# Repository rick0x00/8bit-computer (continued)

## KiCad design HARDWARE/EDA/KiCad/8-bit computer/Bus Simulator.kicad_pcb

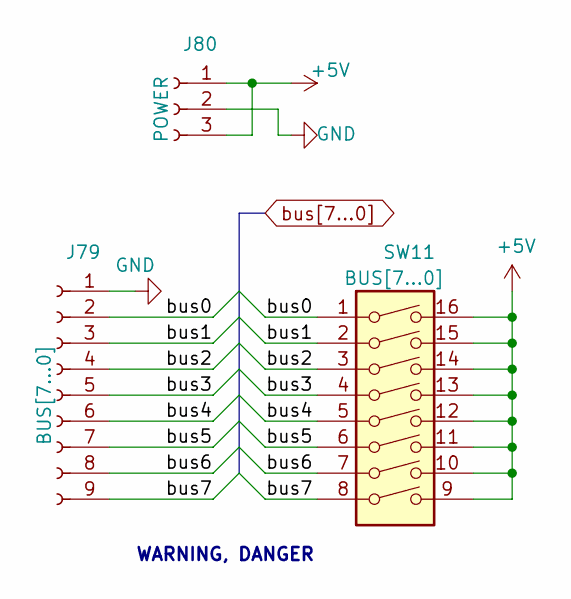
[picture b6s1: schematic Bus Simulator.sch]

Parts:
J79: BUS[7...0]; PinSocket_1x09_P2.00mm_Vertical
J80: POWER; PinSocket_1x03_P2.00mm_Vertical
SW11: BUS[7...0]; SW_DIP_SPSTx08_Slide_9.78x22.5mm_W7.62mm_P2.54mm

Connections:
+5V: J80.1, J80.3, SW11.9, SW11.10, SW11.11, SW11.12, SW11.13, SW11.14, SW11.15, SW11.16
GND: J79.1, J80.2
bus0: J79.2, SW11.1
bus1: J79.3, SW11.2
bus2: J79.4, SW11.3
bus3: J79.5, SW11.4
bus4: J79.6, SW11.5
bus5: J79.7, SW11.6
bus6: J79.8, SW11.7
bus7: J79.9, SW11.8

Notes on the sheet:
WARNING, DANGER

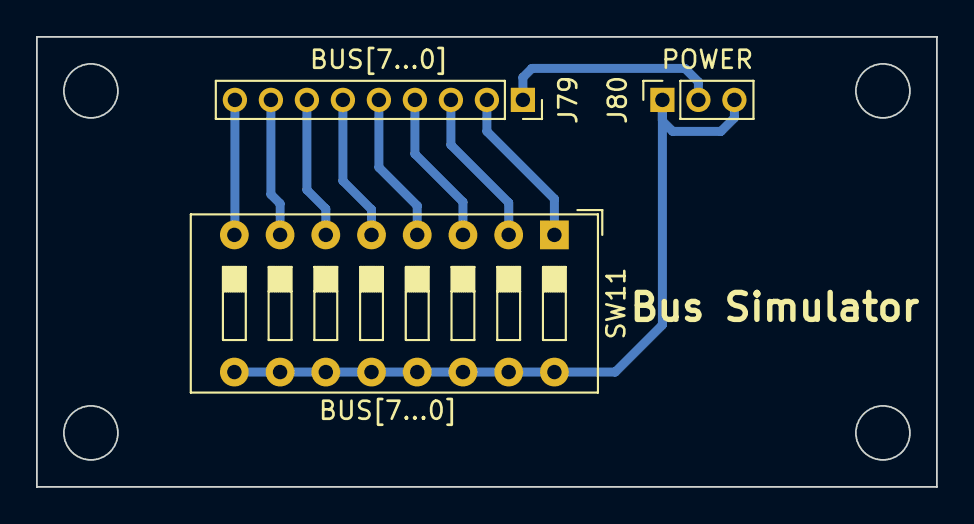
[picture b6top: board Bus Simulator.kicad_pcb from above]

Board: 2 copper layers, 50.0 x 25.0 mm, 3 parts (0 on the bottom side), 10 nets.

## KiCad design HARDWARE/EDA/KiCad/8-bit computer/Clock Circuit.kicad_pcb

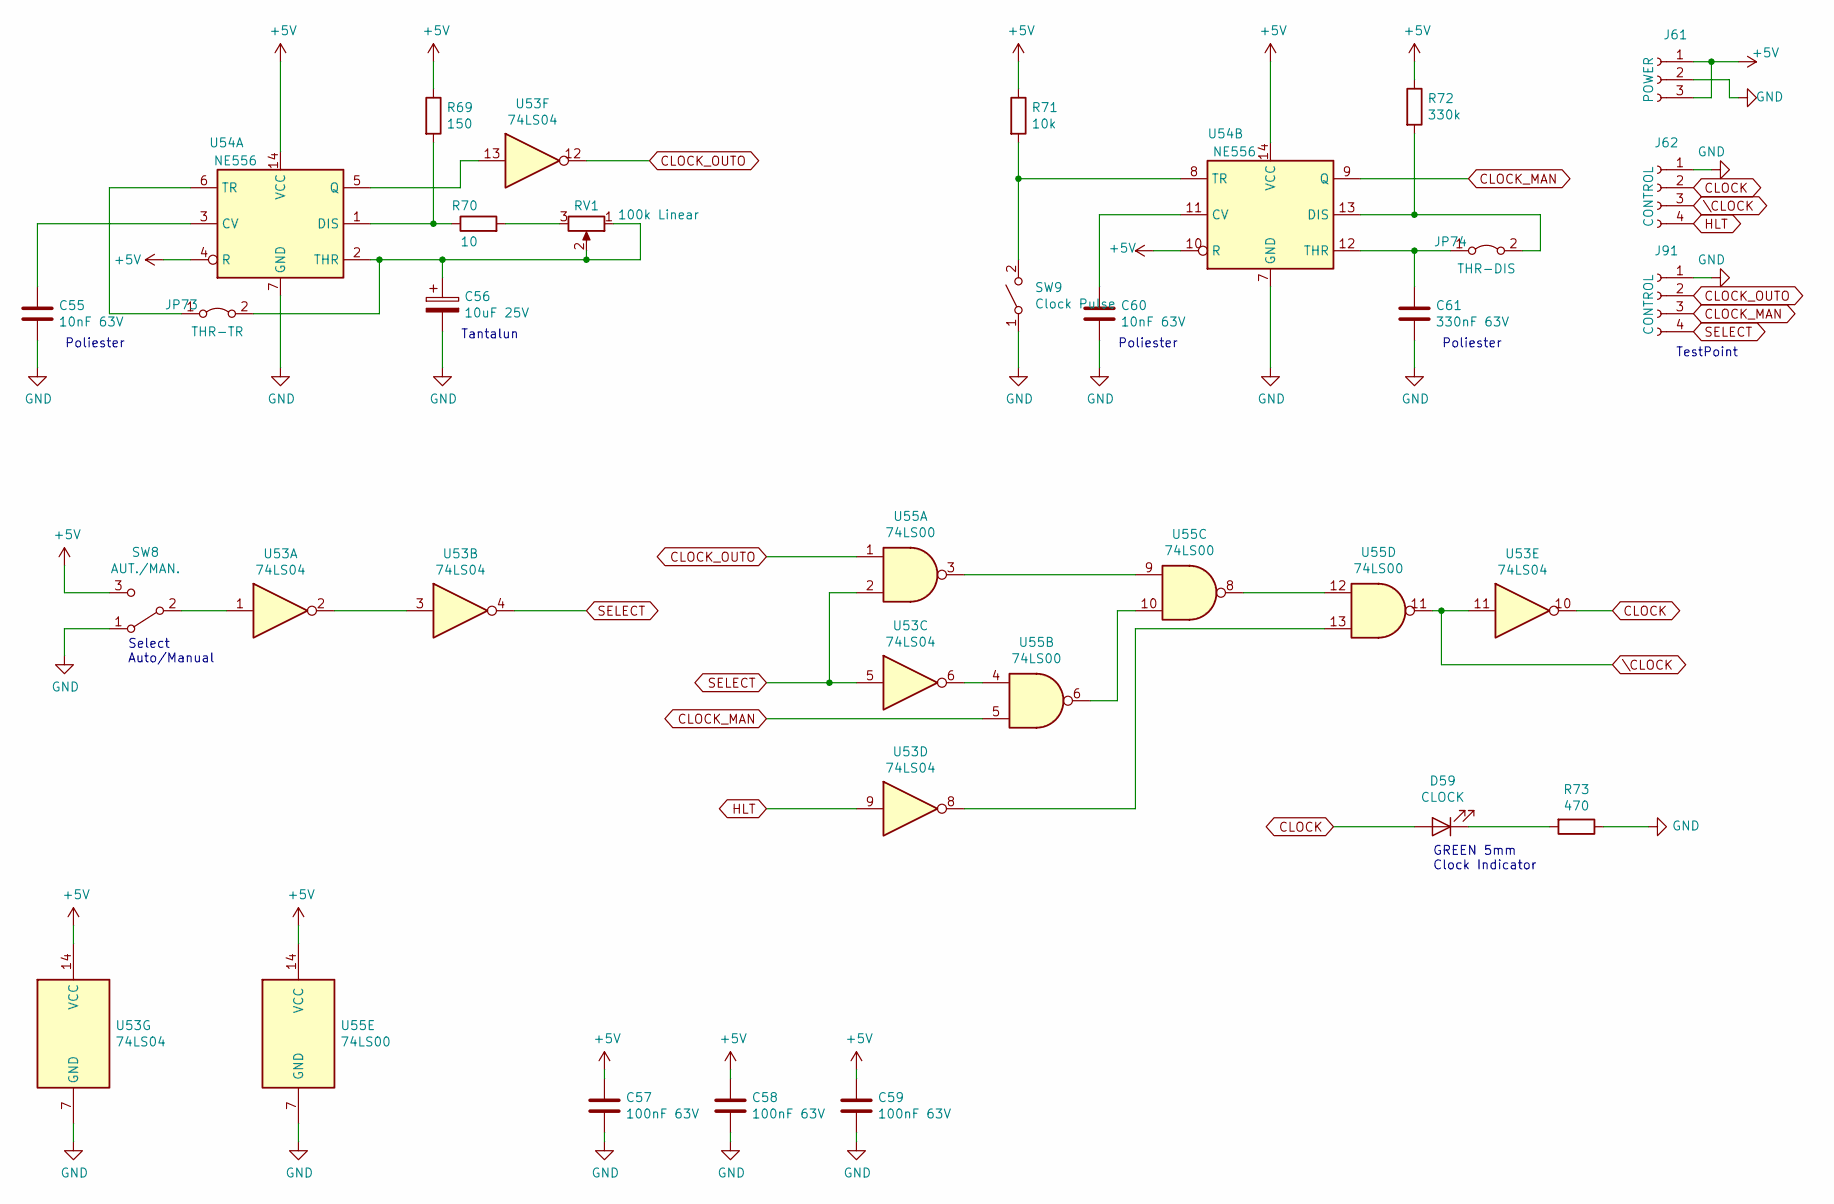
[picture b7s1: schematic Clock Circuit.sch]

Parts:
C55, C60: 10nF 63V; C_Rect_L7.0mm_W2.5mm_P5.00mm
C56: 10uF 25V; CP_Radial_Tantal_D4.5mm_P2.50mm
C57, C58, C59: 100nF 63V; C_Rect_L7.0mm_W2.5mm_P5.00mm
C61: 330nF 63V; C_Rect_L7.0mm_W2.5mm_P5.00mm
D59: CLOCK; LED_D3.0mm
J61: POWER; PinSocket_1x03_P2.00mm_Vertical
J62, J91: CONTROL; PinSocket_1x04_P2.00mm_Vertical
JP73: THR-TR; TestPoint_2Pads_Pitch2.54mm_Drill0.8mm
JP74: THR-DIS; TestPoint_2Pads_Pitch2.54mm_Drill0.8mm
R69: 150; R_Axial_DIN0207_L6.3mm_D2.5mm_P7.62mm_Horizontal
R70: 10; R_Axial_DIN0207_L6.3mm_D2.5mm_P7.62mm_Horizontal
R71: 10k; R_Axial_DIN0207_L6.3mm_D2.5mm_P7.62mm_Horizontal
R72: 330k; R_Axial_DIN0207_L6.3mm_D2.5mm_P7.62mm_Horizontal
R73: 470; R_Axial_DIN0207_L6.3mm_D2.5mm_P7.62mm_Horizontal
RV1: 100k Linear; Potentiometer_Bourns_3266Y_Vertical
SW8: AUT./MAN.; SW_CuK_OS102011MA1QN1_SPDT_Angled
SW9: Clock Pulse; SW_PUSH_6mm_H5mm
U53: 74LS04; DIP-14_W7.62mm_LongPads
U54: NE556; DIP-14_W7.62mm_LongPads
U55: 74LS00; DIP-14_W7.62mm_LongPads

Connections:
+5V: C57.1, C58.1, C59.1, J61.1, J61.3, R69.1, R71.1, R72.1, SW8.3 (C), U53.14 (VCC), U54.4 (R), U54.10 (R), U54.14 (VCC), U55.14 (VCC)
CLOCK: D59.2 (A), J62.2, U53.10
CLOCK_MAN: J91.3, U54.9 (Q), U55.5
CLOCK_OUTO: J91.2, U53.12, U55.1
GND: C55.2, C56.2, C57.2, C58.2, C59.2, C60.2, C61.2, J61.2, J62.1, J91.1, R73.1, SW8.1 (A), SW9.1 (A), U53.7 (GND), U54.7 (GND), U55.7 (GND)
HLT: J62.4, U53.9
unnamed: C55.1, U54.3 (CV)
unnamed: C56.1, JP73.2 (B), RV1.1, RV1.2, U54.2 (THR)
unnamed: C60.1, U54.11 (CV)
unnamed: C61.1, JP74.1 (A), U54.12 (THR)
unnamed: D59.1 (K), R73.2
unnamed: JP73.1 (A), U54.6 (TR)
unnamed: JP74.2 (B), R72.2, U54.13 (DIS)
unnamed: R69.2, R70.1, U54.1 (DIS)
unnamed: R70.2, RV1.3
unnamed: R71.2, SW9.2 (B), U54.8 (TR)
unnamed: SW8.2 (B), U53.1
unnamed: U53.2, U53.3
unnamed: U53.6, U55.4
unnamed: U53.8, U55.13
unnamed: U53.13, U54.5 (Q)
unnamed: U55.3, U55.9
unnamed: U55.6, U55.10
unnamed: U55.8, U55.12
SELECT: J91.4, U53.4, U53.5, U55.2
\CLOCK: J62.3, U53.11, U55.11

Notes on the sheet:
Select Auto/Manual
GREEN 5mm Clock Indicator
Tantalun
Poliester
TestPoint

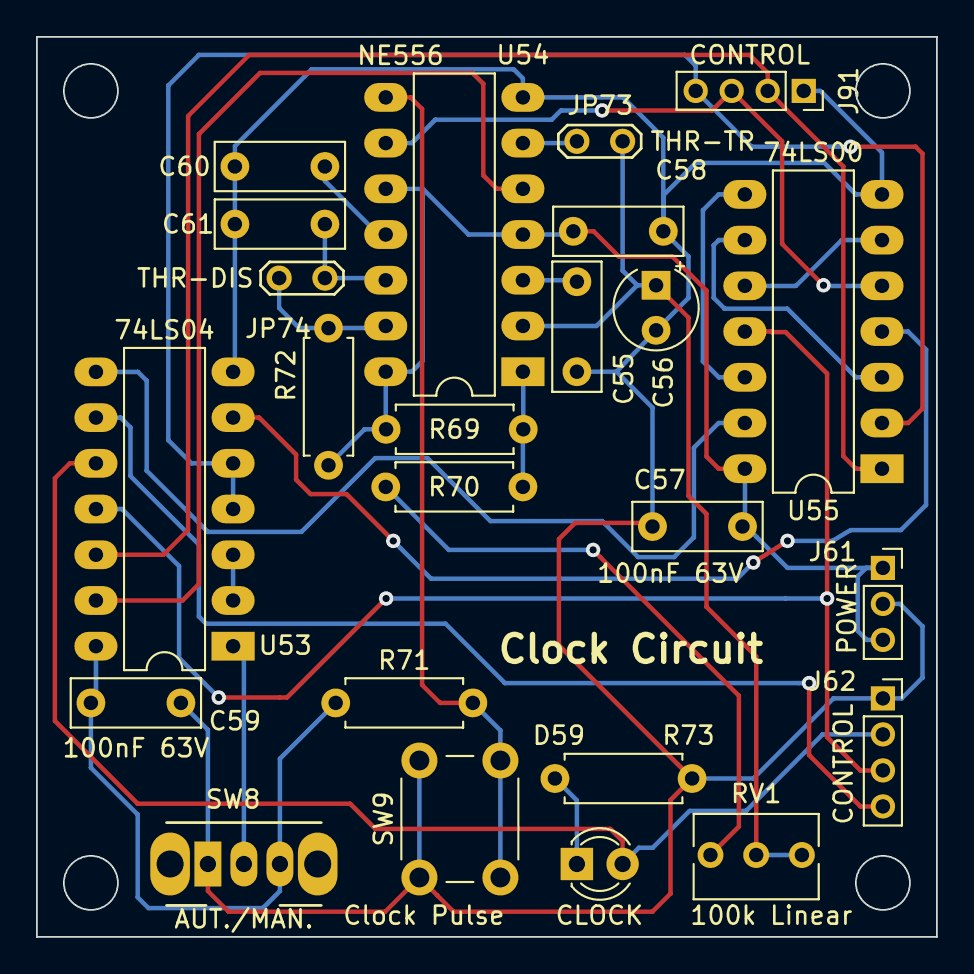
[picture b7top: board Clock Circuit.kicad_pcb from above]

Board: 2 copper layers, 50.0 x 50.0 mm, 24 parts (0 on the bottom side), 26 nets.

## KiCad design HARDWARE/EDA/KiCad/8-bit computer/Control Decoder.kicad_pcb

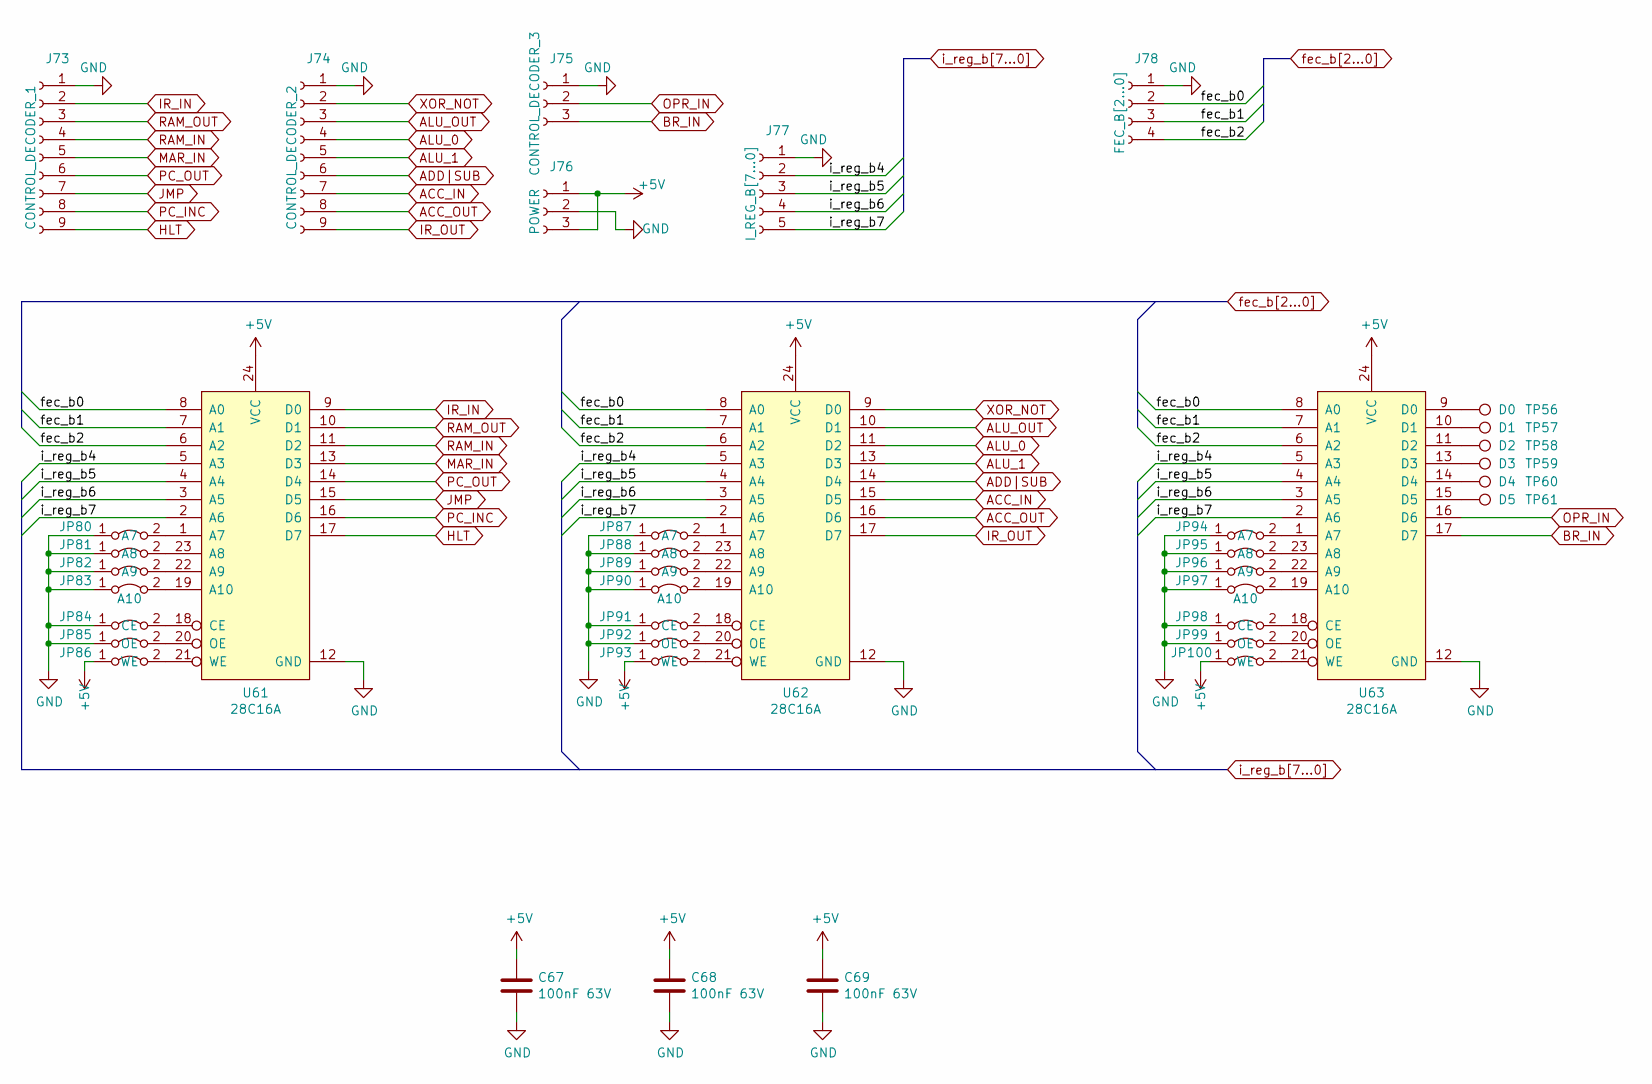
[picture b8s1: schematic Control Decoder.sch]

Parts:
C67, C68, C69: 100nF 63V; C_Rect_L7.0mm_W2.5mm_P5.00mm
J73: CONTROL_DECODER_1; PinSocket_1x09_P2.00mm_Vertical
J74: CONTROL_DECODER_2; PinSocket_1x09_P2.00mm_Vertical
J75: CONTROL_DECODER_3; PinSocket_1x03_P2.00mm_Vertical
J76: POWER; PinSocket_1x03_P2.00mm_Vertical
J77: I_REG_B[7...0]; PinSocket_1x05_P2.00mm_Vertical
J78: FEC_B[2...0]; PinSocket_1x04_P2.00mm_Vertical
JP80, JP87, JP94: A7; TestPoint_2Pads_Pitch2.54mm_Drill0.8mm
JP81, JP88, JP95: A8; TestPoint_2Pads_Pitch2.54mm_Drill0.8mm
JP82, JP89, JP96: A9; TestPoint_2Pads_Pitch2.54mm_Drill0.8mm
JP83, JP90, JP97: A10; TestPoint_2Pads_Pitch2.54mm_Drill0.8mm
JP84, JP91, JP98: CE; TestPoint_2Pads_Pitch2.54mm_Drill0.8mm
JP85, JP92, JP99: OE; TestPoint_2Pads_Pitch2.54mm_Drill0.8mm
JP86, JP93, JP100: WE; TestPoint_2Pads_Pitch2.54mm_Drill0.8mm
TP56: D0; TestPoint_THTPad_D1.5mm_Drill0.7mm
TP57: D1; TestPoint_THTPad_D1.5mm_Drill0.7mm
TP58: D2; TestPoint_THTPad_D1.5mm_Drill0.7mm
TP59: D3; TestPoint_THTPad_D1.5mm_Drill0.7mm
TP60: D4; TestPoint_THTPad_D1.5mm_Drill0.7mm
TP61: D5; TestPoint_THTPad_D1.5mm_Drill0.7mm
U61, U62, U63: 28C16A; DIP-24_W15.24mm_LongPads

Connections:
+5V: C67.1, C68.1, C69.1, J76.1, J76.3, JP86.1 (A), JP93.1 (A), JP100.1 (A), U61.24 (VCC), U62.24 (VCC), U63.24 (VCC)
ACC_IN: J74.7, U62.15 (D5)
ACC_OUT: J74.8, U62.16 (D6)
ADD|SUB: J74.6, U62.14 (D4)
ALU_0: J74.4, U62.11 (D2)
ALU_1: J74.5, U62.13 (D3)
ALU_OUT: J74.3, U62.10 (D1)
BR_IN: J75.3, U63.17 (D7)
GND: C67.2, C68.2, C69.2, J73.1, J74.1, J75.1, J76.2, J77.1, J78.1, JP80.1 (A), JP81.1 (A), JP82.1 (A), JP83.1 (A), JP84.1 (A), JP85.1 (A), JP87.1 (A), JP88.1 (A), JP89.1 (A), JP90.1 (A), JP91.1 (A), JP92.1 (A), JP94.1 (A), JP95.1 (A), JP96.1 (A), JP97.1 (A), JP98.1 (A), JP99.1 (A), U61.12 (GND), U62.12 (GND), U63.12 (GND)
HLT: J73.9, U61.17 (D7)
IR_IN: J73.2, U61.9 (D0)
IR_OUT: J74.9, U62.17 (D7)
JMP: J73.7, U61.15 (D5)
MAR_IN: J73.5, U61.13 (D3)
unnamed: JP80.2 (B), U61.1 (A7)
unnamed: JP81.2 (B), U61.23 (A8)
unnamed: JP82.2 (B), U61.22 (A9)
unnamed: JP83.2 (B), U61.19 (A10)
unnamed: JP84.2 (B), U61.18 (CE)
unnamed: JP85.2 (B), U61.20 (OE)
unnamed: JP86.2 (B), U61.21 (WE)
unnamed: JP87.2 (B), U62.1 (A7)
unnamed: JP88.2 (B), U62.23 (A8)
unnamed: JP89.2 (B), U62.22 (A9)
unnamed: JP90.2 (B), U62.19 (A10)
unnamed: JP91.2 (B), U62.18 (CE)
unnamed: JP92.2 (B), U62.20 (OE)
unnamed: JP93.2 (B), U62.21 (WE)
unnamed: JP94.2 (B), U63.1 (A7)
unnamed: JP95.2 (B), U63.23 (A8)
unnamed: JP96.2 (B), U63.22 (A9)
unnamed: JP97.2 (B), U63.19 (A10)
unnamed: JP98.2 (B), U63.18 (CE)
unnamed: JP99.2 (B), U63.20 (OE)
unnamed: JP100.2 (B), U63.21 (WE)
unnamed: TP56.1, U63.9 (D0)
unnamed: TP57.1, U63.10 (D1)
unnamed: TP58.1, U63.11 (D2)
unnamed: TP59.1, U63.13 (D3)
unnamed: TP60.1, U63.14 (D4)
unnamed: TP61.1, U63.15 (D5)
OPR_IN: J75.2, U63.16 (D6)
PC_INC: J73.8, U61.16 (D6)
PC_OUT: J73.6, U61.14 (D4)
RAM_IN: J73.4, U61.11 (D2)
RAM_OUT: J73.3, U61.10 (D1)
XOR_NOT: J74.2, U62.9 (D0)
fec_b0: J78.2, U61.8 (A0), U62.8 (A0), U63.8 (A0)
fec_b1: J78.3, U61.7 (A1), U62.7 (A1), U63.7 (A1)
fec_b2: J78.4, U61.6 (A2), U62.6 (A2), U63.6 (A2)
i_reg_b4: J77.2, U61.5 (A3), U62.5 (A3), U63.5 (A3)
i_reg_b5: J77.3, U61.4 (A4), U62.4 (A4), U63.4 (A4)
i_reg_b6: J77.4, U61.3 (A5), U62.3 (A5), U63.3 (A5)
i_reg_b7: J77.5, U61.2 (A6), U62.2 (A6), U63.2 (A6)

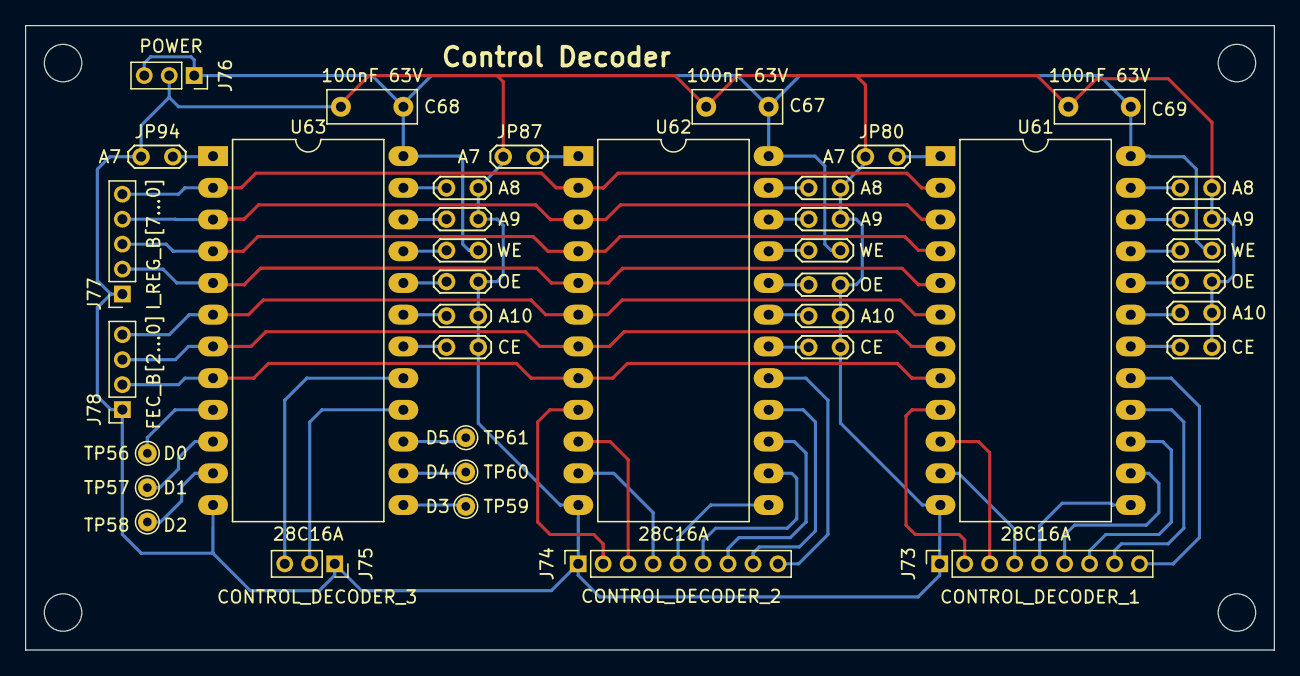
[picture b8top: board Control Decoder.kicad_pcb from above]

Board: 2 copper layers, 100.0 x 50.0 mm, 39 parts (0 on the bottom side), 54 nets.
